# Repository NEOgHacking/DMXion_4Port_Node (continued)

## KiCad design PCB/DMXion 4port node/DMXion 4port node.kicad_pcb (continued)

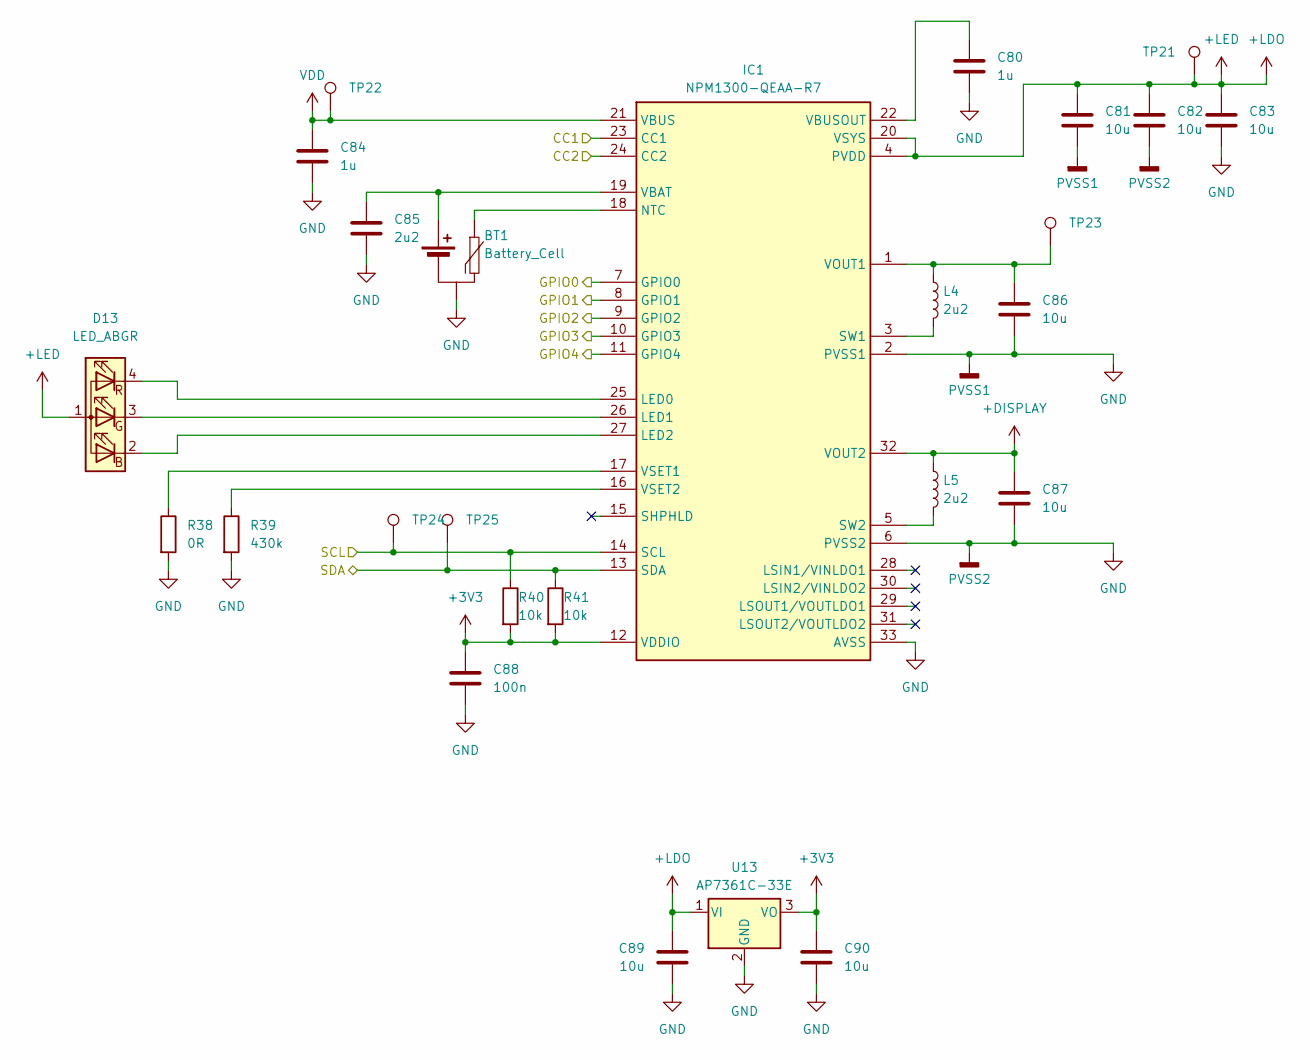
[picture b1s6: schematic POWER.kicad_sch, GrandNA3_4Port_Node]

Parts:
BT1: Battery_Cell; JST_XH_B3B-XH-A_1x03_P2.50mm_Vertical
C80, C84: 1u; C_0603_1608Metric
C81, C82, C83, C86, C87, C89, C90: 10u; C_0603_1608Metric
C85: 2u2; C_0603_1608Metric
C88: 100n; C_0603_1608Metric
D13: LED_ABGR; LED-SMD_4P-L1.6-W1.5-TR
IC1: NPM1300-QEAA-R7; QFN-32-1EP_5x5mm_P0.5mm_EP3.45x3.45mm_ThermalVias; Mouser Part Number 949-NPM1300-QEAA-R7
L4, L5: 2u2; L_0805_2012Metric
R38: 0R; R_0603_1608Metric
R39: 430k; R_0603_1608Metric
R40, R41: 10k; R_0603_1608Metric
TP21, TP22, TP23, TP24, TP25: TestPoint; TestPoint_Pad_D1.5mm
U13: AP7361C-33E; SOT-223-3_TabPin2

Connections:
+3V3: C88.1, C90.1, IC1.12 (VDDIO), R40.2, R41.2, U13.3 (VO); also elsewhere on the board
+DISPLAY: C87.1, IC1.32 (VOUT2), L5.1; also elsewhere on the board
+LDO: C81.1, C82.1, C83.1, C89.1, D13.1 (A), IC1.4 (PVDD), IC1.20 (VSYS), TP21.1 (1_1), U13.1 (VI); also elsewhere on the board
/Microcontroller/GPIO16: IC1.11 (GPIO4); also elsewhere on the board
/Microcontroller/GPIO17: IC1.10 (GPIO3); also elsewhere on the board
/Microcontroller/GPIO18: IC1.9 (GPIO2); also elsewhere on the board
/Microcontroller/GPIO19: IC1.8 (GPIO1); also elsewhere on the board
/Microcontroller/GPIO20: IC1.7 (GPIO0); also elsewhere on the board
/Microcontroller/GPIO22_I2C1_SDA: IC1.13 (SDA), R41.1, TP25.1 (1_1); also elsewhere on the board
/Microcontroller/GPIO23_I2C_SCL: IC1.14 (SCL), R40.1, TP24.1 (1_1); also elsewhere on the board
/POWER/CC1: IC1.23 (CC1); also elsewhere on the board
/POWER/CC2: IC1.24 (CC2); also elsewhere on the board
GND: BT1.2 (-), C80.2, C81.2, C82.2, C83.2, C84.2, C85.2, C86.2, C87.2, C88.2, C89.2, C90.2, IC1.2 (PVSS1), IC1.6 (PVSS2), IC1.33 (AVSS), R38.2, R39.2, U13.2 (GND); also elsewhere on the board
unnamed: BT1.1 (+), C85.1, IC1.19 (VBAT)
unnamed: BT1.3 (NTC), IC1.18 (NTC)
unnamed: D13.2 (BK), IC1.27 (LED2)
unnamed: D13.3 (GK), IC1.26 (LED1)
unnamed: D13.4 (RK), IC1.25 (LED0)
unnamed: IC1.3 (SW1), L4.2
unnamed: IC1.5 (SW2), L5.2
unnamed: C80.1, IC1.22 (VBUSOUT)
unnamed: C86.1, IC1.1 (VOUT1), L4.1, TP23.1 (1_1)
unnamed: IC1.17 (VSET1), R38.1
unnamed: IC1.16 (VSET2), R39.1
VDD: C84.1, IC1.21 (VBUS), TP22.1 (1_1); also elsewhere on the board

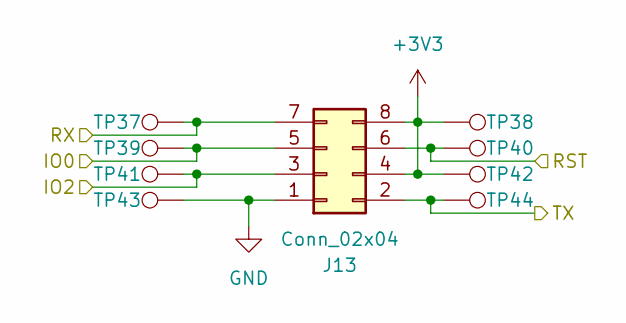
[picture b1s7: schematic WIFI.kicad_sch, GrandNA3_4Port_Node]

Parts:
J13: Conn_02x04; PinSocket_2x04_P2.54mm_Vertical
TP37, TP38, TP39, TP40, TP41, TP42, TP43, TP44: TestPoint; TestPoint_Pad_D1.5mm

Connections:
+3V3: J13.4, J13.8, TP38.1 (1_1), TP42.1 (1_1); also elsewhere on the board
/Microcontroller/GPIO11: J13.3, TP41.1 (1_1); also elsewhere on the board
/Microcontroller/GPIO12: J13.5, TP39.1 (1_1); also elsewhere on the board
/Microcontroller/GPIO13: J13.6, TP40.1 (1_1); also elsewhere on the board
/Microcontroller/GPIO14_UART1_TX: J13.7, TP37.1 (1_1); also elsewhere on the board
/Microcontroller/GPIO15_UART1_RX: J13.2, TP44.1 (1_1); also elsewhere on the board
GND: J13.1, TP43.1 (1_1); also elsewhere on the board

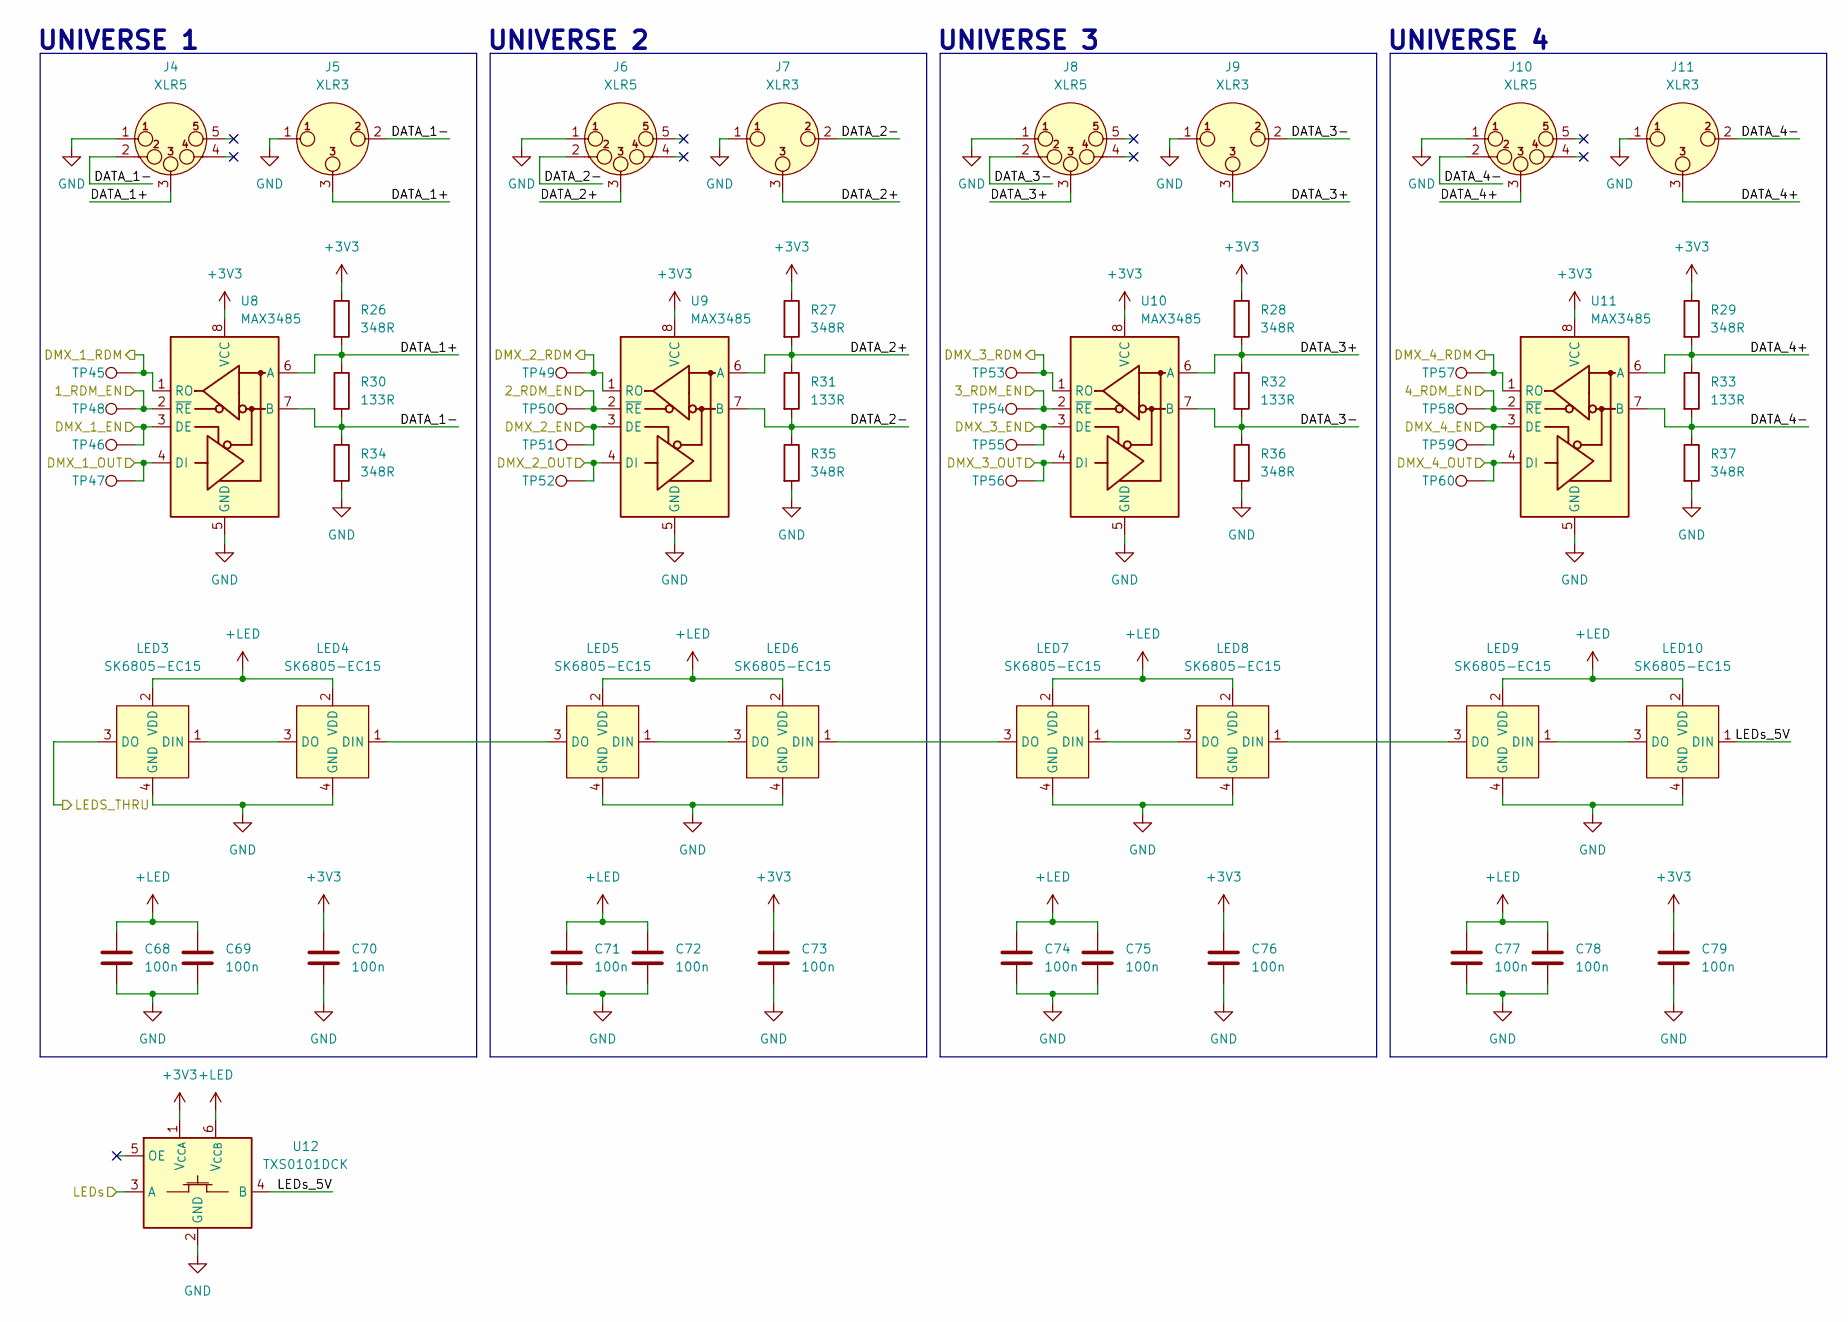
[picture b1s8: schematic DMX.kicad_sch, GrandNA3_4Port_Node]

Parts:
C68, C69, C70, C71, C72, C73, C74, C75, C76, C77, C78, C79: 100n; C_0603_1608Metric
J4, J6, J8, J10: XLR5; NC5FAH1-LR-DAE
J5, J7, J9, J11: XLR3; NC3FAH2-LR-DAE
LED3, LED4, LED5, LED6, LED7, LED8, LED9, LED10: SK6805-EC15; LED-SMD_4P-L1.5-W1.5-BL; LCSC Part C2890035
R26, R27, R28, R29, R34, R35, R36, R37: 348R; R_0603_1608Metric
R30, R31, R32, R33: 133R; R_0603_1608Metric
TP45, TP46, TP47, TP48, TP49, TP50, TP51, TP52, TP53, TP54, TP55, TP56, TP57, TP58, TP59, TP60: TestPoint; TestPoint_Pad_D1.5mm
U8, U9, U10, U11: MAX3485; SOIC-8_3.9x4.9mm_P1.27mm
U12: TXS0101DCK; SOT-363_SC-70-6

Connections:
+3V3: C70.1, C73.1, C76.1, C79.1, R26.1, R27.1, R28.1, R29.1, U8.8 (VCC), U9.8 (VCC), U10.8 (VCC), U11.8 (VCC), U12.1 (V_{CCA}); also elsewhere on the board
+LDO: C68.1, C69.1, C71.1, C72.1, C74.1, C75.1, C77.1, C78.1, LED3.2 (VDD), LED4.2 (VDD), LED5.2 (VDD), LED6.2 (VDD), LED7.2 (VDD), LED8.2 (VDD), LED9.2 (VDD), LED10.2 (VDD), U12.6 (V_{CCB}); also elsewhere on the board
/DMX/1_RDM_EN: TP48.1 (1_1), U8.2 (~RE); also elsewhere on the board
/DMX/2_RDM_EN: TP50.1 (1_1), U9.2 (~RE); also elsewhere on the board
/DMX/3_RDM_EN: TP54.1 (1_1), U10.2 (~RE); also elsewhere on the board
/DMX/4_RDM_EN: TP58.1 (1_1), U11.2 (~RE); also elsewhere on the board
/DMX/DATA_1+: J4.3, J5.3, R26.2, R30.1, U8.6 (A)
/DMX/DATA_1-: J4.2, J5.2, R30.2, R34.1, U8.7 (B)
/DMX/DATA_2+: J6.3, J7.3, R27.2, R31.1, U9.6 (A)
/DMX/DATA_2-: J6.2, J7.2, R31.2, R35.1, U9.7 (B)
/DMX/DATA_3+: J8.3, J9.3, R28.2, R32.1, U10.6 (A)
/DMX/DATA_3-: J8.2, J9.2, R32.2, R36.1, U10.7 (B)
/DMX/DATA_4+: J10.3, J11.3, R29.2, R33.1, U11.6 (A)
/DMX/DATA_4-: J10.2, J11.2, R33.2, R37.1, U11.7 (B)
/DMX/DMX_1_EN: TP46.1 (1_1), U8.3 (DE); also elsewhere on the board
/DMX/DMX_1_OUT: TP47.1 (1_1), U8.4 (DI); also elsewhere on the board
/DMX/DMX_1_RDM: TP45.1 (1_1), U8.1 (RO); also elsewhere on the board
/DMX/DMX_2_EN: TP51.1 (1_1), U9.3 (DE); also elsewhere on the board
/DMX/DMX_2_OUT: TP52.1 (1_1), U9.4 (DI); also elsewhere on the board
/DMX/DMX_2_RDM: TP49.1 (1_1), U9.1 (RO); also elsewhere on the board
/DMX/DMX_3_EN: TP55.1 (1_1), U10.3 (DE); also elsewhere on the board
/DMX/DMX_3_OUT: TP56.1 (1_1), U10.4 (DI); also elsewhere on the board
/DMX/DMX_3_RDM: TP53.1 (1_1), U10.1 (RO); also elsewhere on the board
/DMX/DMX_4_EN: TP59.1 (1_1), U11.3 (DE); also elsewhere on the board
/DMX/DMX_4_OUT: TP60.1 (1_1), U11.4 (DI); also elsewhere on the board
/DMX/DMX_4_RDM: TP57.1 (1_1), U11.1 (RO); also elsewhere on the board
/DMX/LEDs: U12.3 (A); also elsewhere on the board
/DMX/LEDs_5V: LED10.1 (DIN), U12.4 (B)
/LEDS_THRU: LED3.3 (DO); also elsewhere on the board
GND: C68.2, C69.2, C70.2, C71.2, C72.2, C73.2, C74.2, C75.2, C76.2, C77.2, C78.2, C79.2, J4.1, J5.1, J6.1, J7.1, J8.1, J9.1, J10.1, J11.1, LED3.4 (GND), LED4.4 (GND), LED5.4 (GND), LED6.4 (GND), LED7.4 (GND), LED8.4 (GND), LED9.4 (GND), LED10.4 (GND), R34.2, R35.2, R36.2, R37.2, U8.5 (GND), U9.5 (GND), U10.5 (GND), U11.5 (GND), U12.2 (GND); also elsewhere on the board
unnamed: LED3.1 (DIN), LED4.3 (DO)
unnamed: LED4.1 (DIN), LED5.3 (DO)
unnamed: LED5.1 (DIN), LED6.3 (DO)
unnamed: LED6.1 (DIN), LED7.3 (DO)
unnamed: LED7.1 (DIN), LED8.3 (DO)
unnamed: LED8.1 (DIN), LED9.3 (DO)
unnamed: LED9.1 (DIN), LED10.3 (DO)

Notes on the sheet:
UNIVERSE 1
UNIVERSE 3
UNIVERSE 4
UNIVERSE 2

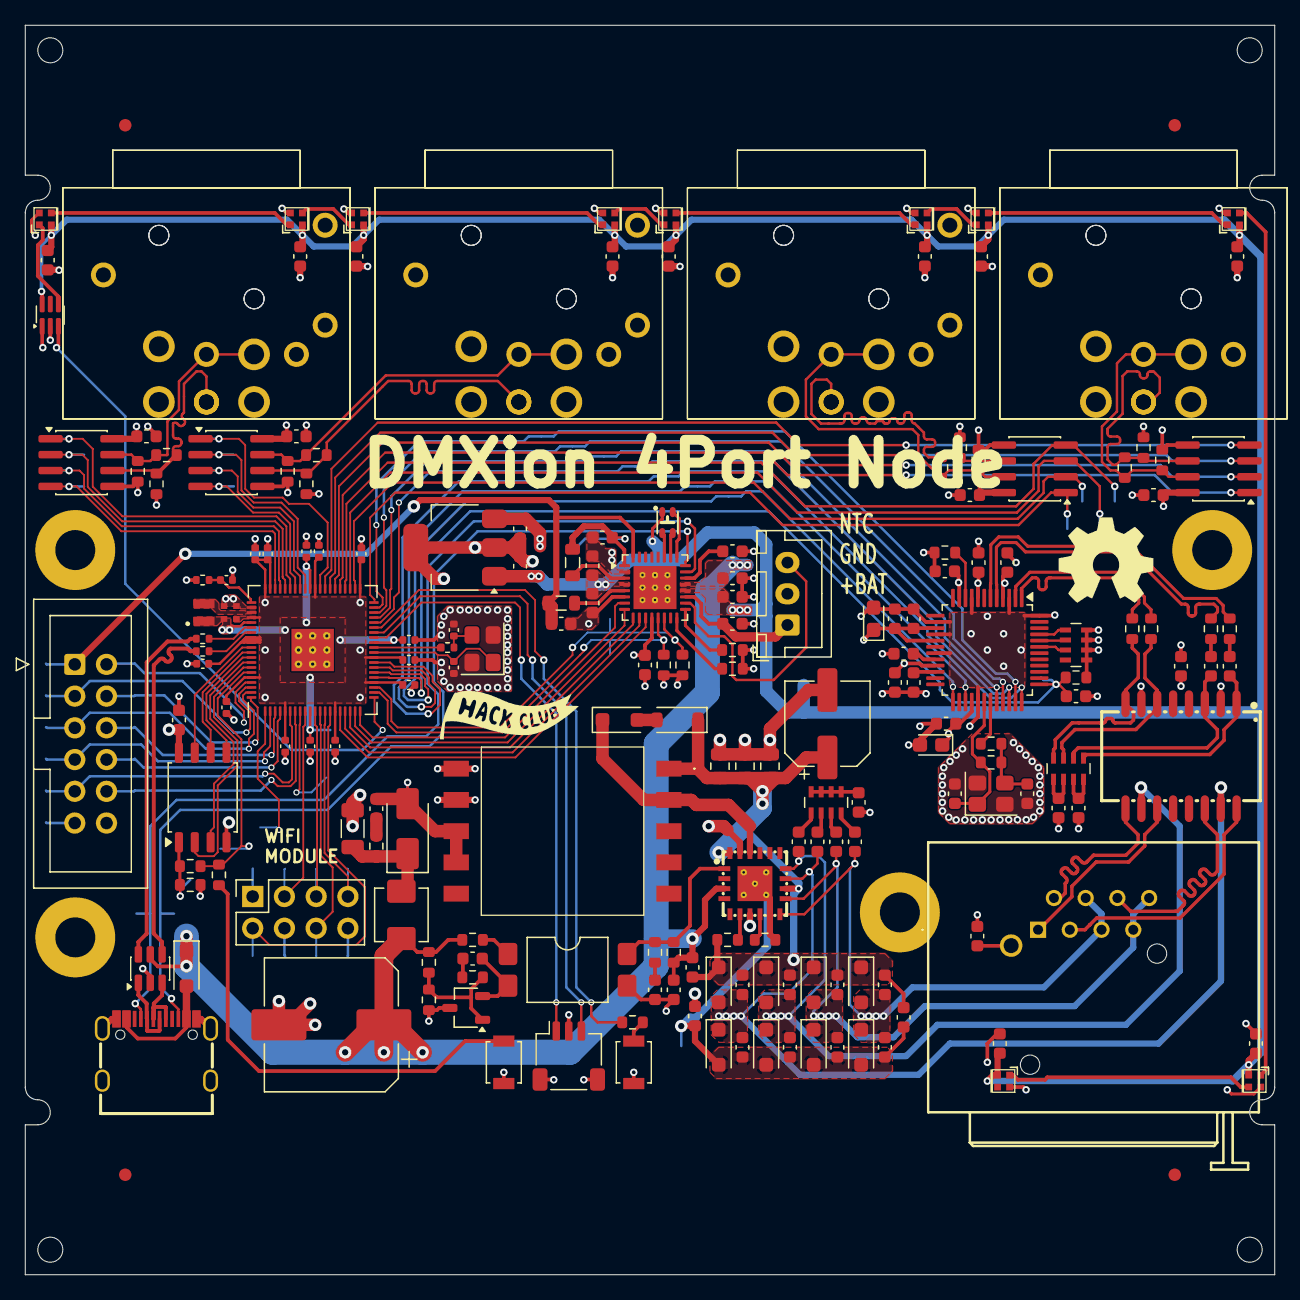
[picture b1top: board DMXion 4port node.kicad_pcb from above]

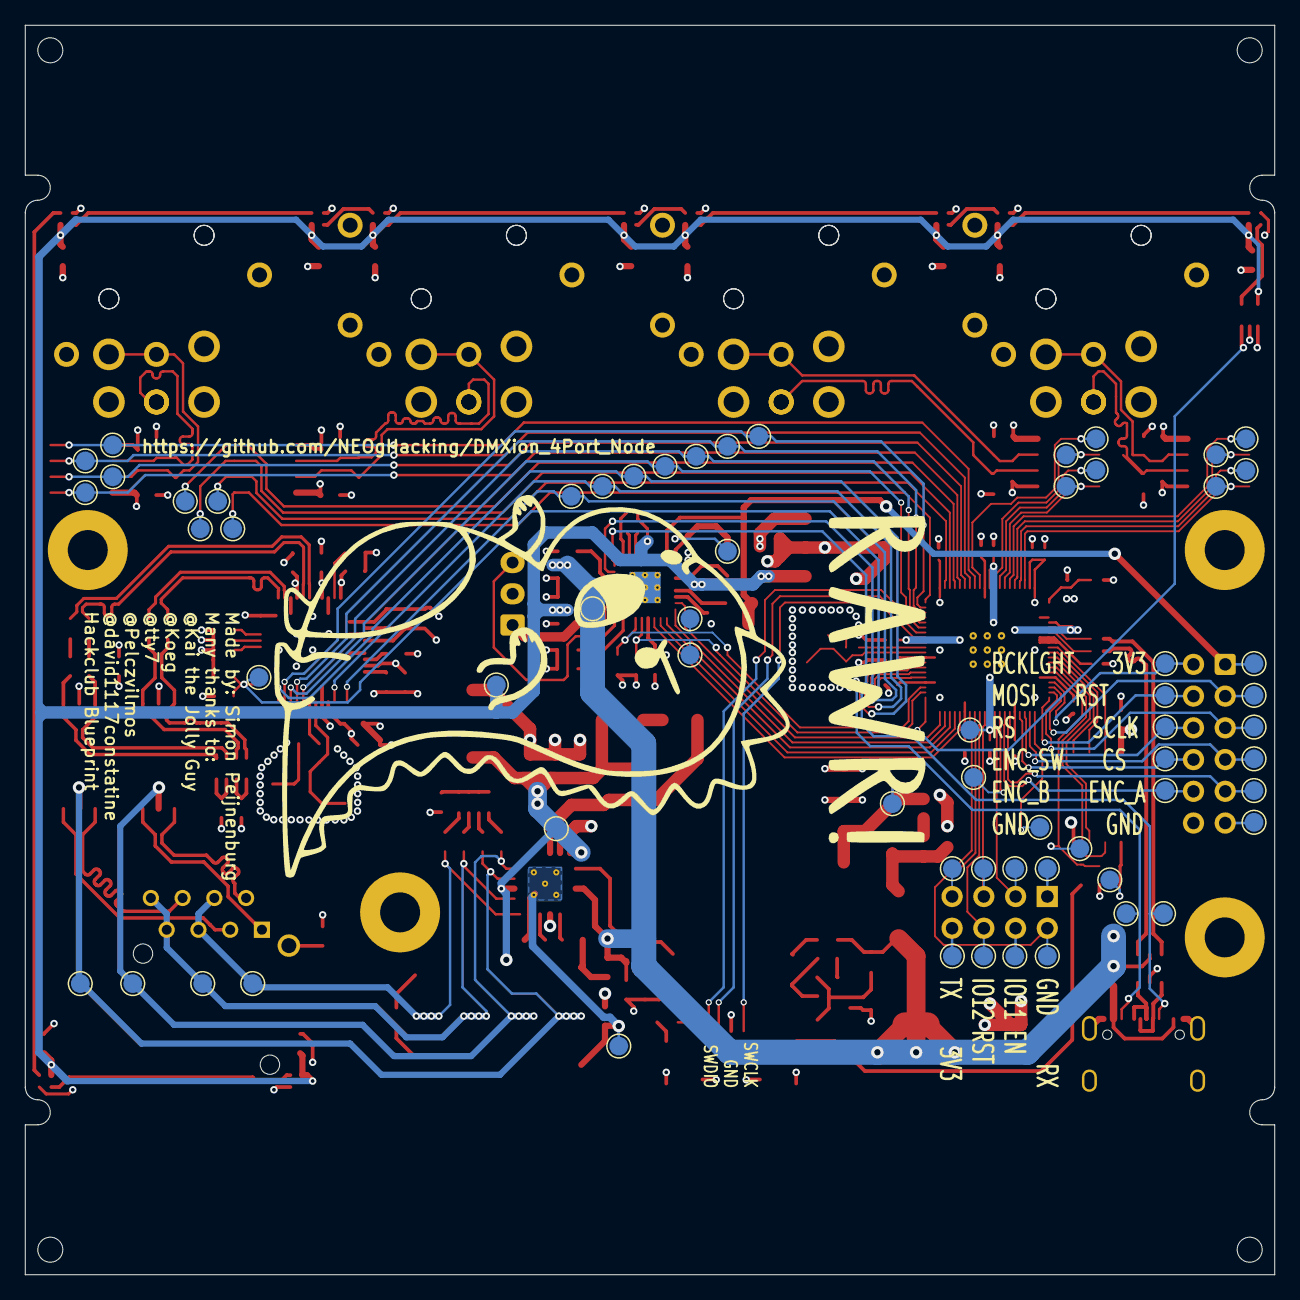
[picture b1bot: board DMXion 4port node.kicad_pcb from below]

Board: 4 copper layers, 100.0 x 100.0 mm, 269 parts (62 on the bottom side), 160 nets.

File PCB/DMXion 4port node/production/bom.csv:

Designator,Footprint,Quantity,Value,LCSC Part #
BT1,JST_XH_B3B-XH-A_1x03_P2.50mm_Vertical,1,Battery_Cell,
"C1, C10, C11, C12, C13, C3, C4, C5, C6, C7, C8, C9",0402,12,100n,
"C14, C15, C16, C2",0402,4,4u7,
"C17, C19",0402,2,15p,
"C18, C25, C26, C27, C28, C29, C30, C31, C38, C39, C41, C60, C61, C64, C66, C67, C68, C69, C70, C71, C72, C73, C74, C75, C76, C77, C78, C79, C88",0603,29,100n,
"C20, C21, C23, C33, C57",0603,5,10n,
"C22, C34, C35, C36, C37, C43, C44, C45, C46, C47, C63, C65",0603,12,1n,
"C24, C32",CP_EIA-2012-12_Kemet-R,2,10u,
"C40, C42",0603,2,6.8n,
"C48, C49",0603,2,10p,
"C50, C51, C52",0805,3,1u,
C53,CP_Elec_6.3x5.8,1,10u,
C54,0603,1,470p,
C55,CP_Elec_10x10.5,1,1000u,
C56,1206,1,100u,
C58,0603,1,4u7,
C59,0603,1,3.3n,
C62,0603,1,15n,
"C80, C84",0603,2,1u,
"C81, C82, C83, C86, C87, C89, C90",0603,7,10u,
C85,0603,1,2u2,
D1,D_SOD-123F,1,DSK24L,
D10,D_SMA,1,SS34,
D11,D_SOD-123,1,1N4148W,
D12,D_SOD-123F,1,DFTL30A,
D13,LED-SMD_4P-L1.6-W1.5-TR,1,LED_ABGR,
"D2, D3, D4, D5, D6, D7, D8, D9",D_SOD-123F,8,SL110PL-TP,
IC1,QFN-32-1EP_5x5mm_P0.5mm_EP3.45x3.45mm_ThermalVias,1,NPM1300-QEAA-R7,
J1,JST_SH_SM03B-SRSS-TB_1x03-1MP_P1.00mm_Horizontal,1,Conn_01x03_MountingPin,
"J10, J4, J6, J8",NC5FAH1-LR-DAE,4,XLR5,
"J11, J5, J7, J9",NC3FAH2-LR-DAE,4,XLR3,
J12,IDC-Header_2x06_P2.54mm_Vertical,1,IDC,
J13,PinSocket_2x04_P2.54mm_Vertical,1,Conn_02x04,
J2,USB-C_SMD-TYPE-C-31-M-12_1,1,USB_C_Receptacle_USB2.0_14P,
J3,NE8FAHLRDAE,1,RJ45,
L1,L_pol_2016,1,3.3u,
L2,L_Vishay_IHLP-1616,1,1u,
L3,XFMR-SMD_16P-L12.7-W7.1-P1.27-LS9.4-BL,1,H2019NLT,C110250
"L4, L5",0805,2,2u2,
"LED1, LED10, LED2, LED3, LED4, LED5, LED6, LED7, LED8, LED9",LED-SMD_4P-L1.5-W1.5-BL,10,SK6805-EC15,C2890035
"R1, R25, R3",0603,3,1k,
"R10, R11, R12, R13",0603,4,33R,
R14,0603,1,1M,
"R15, R20, R21, R38, R8",0603,5,0R,
R16,0603,1,10R,
R17,0603,1,12.4k,
R18,0603,1,4.99k,
R19,0603,1,2.05k,
R2,0402,1,33R,
R22,0603,1,36.5k,
R23,0603,1,12.1k,
R24,0603,1,24.9k,
"R26, R27, R28, R29, R34, R35, R36, R37",0603,8,348R,
"R30, R31, R32, R33",0603,4,133R,
R39,0603,1,430k,
"R4, R5",0402,2,27R,
"R40, R41, R7, R9",0603,4,10k,
R6,0402,1,1k,
"RN1, RN2",R_Array_Concave_4x0603,2,75R,
RN3,R_Array_Concave_4x0603,1,10k,
"SW1, SW2",SW_SPST_B3U-1000P,2,SW_Push,
T1,FA2924ALD,1,FA2805,
"TP1, TP10, TP11, TP12, TP13, TP14, TP15, TP16, TP17, TP18, TP19, TP2, TP20, TP21, TP22, TP23, TP24, TP25, TP26, TP27, TP28, TP29, TP3, TP30, TP31, TP32, TP33, TP34, TP35, TP36, TP37, TP38, TP39, TP4, TP40, TP41, TP42, TP43, TP44, TP45, TP46, TP47, TP48, TP49, TP5, TP50, TP51, TP52, TP53, TP54, TP55, TP56, TP57, TP58, TP59, TP6, TP60, TP61, TP62, TP7, TP8, TP9",TestPoint_Pad_D1.5mm,62,TestPoint,
U1,RP2350-QFN-80-1EP_10x10_P0.4mm_EP3.4x3.4mm_ThermalVias,1,RP2350B,
"U10, U11, U8, U9",SOIC-8_3.9x4.9mm_P1.27mm,4,MAX3485,
U12,SOT-363_SC-70-6,1,TXS0101DCK,
U13,SOT-223-3_TabPin2,1,AP7361C-33E,
U2,SOIC-8_5.3x5.3mm_P1.27mm,1,W25Q128JVS,
U3,SOT-23-6,1,USBLC6-2SC6,
U4,LQFP-48_7x7mm_P0.5mm,1,W5500,
U5,SMDIP-4_W9.53mm_Clearance8mm,1,VO618A-3X019T,
U6,QFN-20_L5.0-W5.0-P0.80-TL-EP2.8,1,SI3402-B-GMR,C510771
U7,TSOT-23,1,TLV431,
Y1,Crystal_SMD_3225-4Pin_3.2x2.5mm,1,ABM8-272-T3,
Y2,Crystal_SMD_3225-4Pin_3.2x2.5mm,1,ABM8-25.000MHZ-10-D1G-T,

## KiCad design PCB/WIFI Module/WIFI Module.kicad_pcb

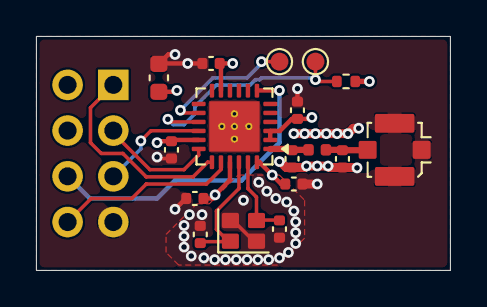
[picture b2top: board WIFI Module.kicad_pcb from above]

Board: 4 copper layers, 23.0 x 13.0 mm, 18 parts (1 on the bottom side), 13 nets.

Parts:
C1: 10u; C_0603_1608Metric
C2, C3, C4, C5, C6: 100n; C_0402_1005Metric
C7, C8: 3p; C_0402_1005Metric
C9, C10: 14p; C_0402_1005Metric
J1: Conn_01x01_Shielded; U.FL_Molex_MCRF_73412-0110_Vertical
J2: Conn_02x04; PinHeader_2x04_P2.54mm_Vertical
L1: 2n; L_0402_1005Metric
R1: 10k; R_0402_1005Metric
TP1, TP2: TestPoint; TestPoint_Pad_D1.0mm
U1: ESP8684; QFN-24-1EP_4x4mm_P0.5mm_EP2.8x2.8mm
Y1: Q22FA12800230; Crystal_SMD_SeikoEpson_FA128-4Pin_2.0x1.6mm

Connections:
+3V3: C1.1, C2.1, C3.1, C4.1, C5.1, C6.1, J2.2, R1.2, U1.2 (VDDA3P3), U1.3 (VDDA3P3), U1.11 (VDD3P3_RTC), U1.17 (VDD3P3_CPU), U1.21 (VDDA), U1.24 (VDDA)
/EN: J2.6, U1.7 (CHIP_EN)
/GPIO9: R1.1, TP2.1, U1.15 (GPIO9/BOOT)
/GPIO10: J2.5, U1.16 (GPIO10/FSPICS0)
/GPIO18: J2.3, U1.18 (GPIO18)
/RX: J2.1, U1.19 (U0RXD/GPIO19)
/TX: J2.8, U1.20 (U0TXD/GPIO20)
GND: C1.2, C2.2, C3.2, C4.2, C5.2, C6.2, C7.2, C8.2, C9.1, C10.1, J1.SH (Shield), J2.7, U1.25 (GND), Y1.2 (G), Y1.4 (G)
unnamed: C7.1, J1.1, L1.1
unnamed: C8.1, L1.2, U1.1 (ANT)
unnamed: TP1.1, U1.14 (GPIO8)
unnamed: C9.2, U1.22 (XTAL_N), Y1.1
unnamed: C10.2, U1.23 (XTAL_P), Y1.3

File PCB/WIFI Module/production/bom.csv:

Designator,Footprint,Quantity,Value,LCSC Part #
"C1_8, C1_7, C1_6, C1_5, C1_4, C1_3, C1_2, C1",0603,8,10u,
"C10_8, C10_7, C10_6, C10_5, C10_4, C10_3, C10_2, C10, C9_8, C9_7, C9_6, C9_5, C9_4, C9_3, C9_2, C9",0402,16,14p,
"C2_8, C2_7, C2_6, C2_5, C2_4, C2_3, C2_2, C2, C3_8, C3_7, C3_6, C3_5, C3_4, C3_3, C3_2, C3, C4_8, C4_7, C4_6, C4_5, C4_4, C4_3, C4_2, C4, C5_8, C5_7, C5_6, C5_5, C5_4, C5_3, C5_2, C5, C6_8, C6_7, C6_6, C6_5, C6_4, C6_3, C6_2, C6",0402,40,100n,
"C7_8, C7_7, C7_6, C7_5, C7_4, C7_3, C7_2, C7, C8_8, C8_7, C8_6, C8_5, C8_4, C8_3, C8_2, C8",0402,16,3p,
"J1_8, J1_7, J1_6, J1_5, J1_4, J1_3, J1_2, J1",U.FL_Molex_MCRF_73412-0110_Vertical,8,Conn_01x01_Shielded,
"J2_8, J2_7, J2_6, J2_5, J2_4, J2_3, J2_2, J2",PinHeader_2x04_P2.54mm_Vertical,8,Conn_02x04,
"L1_8, L1_7, L1_6, L1_5, L1_4, L1_3, L1_2, L1",0402,8,2n,
"R1_8, R1_7, R1_6, R1_5, R1_4, R1_3, R1_2, R1",0402,8,10k,
"TP1_8, TP1_7, TP1_6, TP1_5, TP1_4, TP1_3, TP1_2, TP1, TP2_8, TP2_7, TP2_6, TP2_5, TP2_4, TP2_3, TP2_2, TP2",TestPoint_Pad_D1.0mm,16,TestPoint,
"U1_8, U1_7, U1_6, U1_5, U1_4, U1_3, U1_2, U1",QFN-24-1EP_4x4mm_P0.5mm_EP2.8x2.8mm,8,ESP8684,
"Y1_8, Y1_7, Y1_6, Y1_5, Y1_4, Y1_3, Y1_2, Y1",Crystal_SMD_SeikoEpson_FA128-4Pin_2.0x1.6mm,8,Q22FA12800230,

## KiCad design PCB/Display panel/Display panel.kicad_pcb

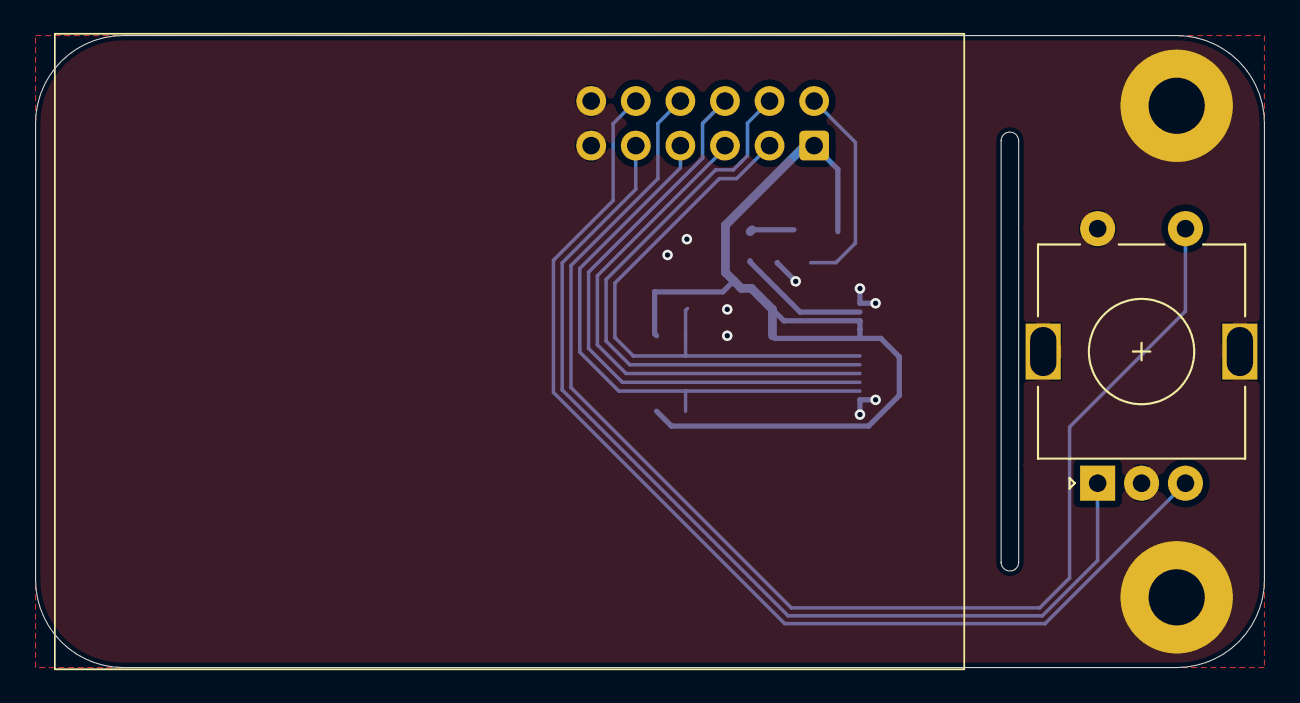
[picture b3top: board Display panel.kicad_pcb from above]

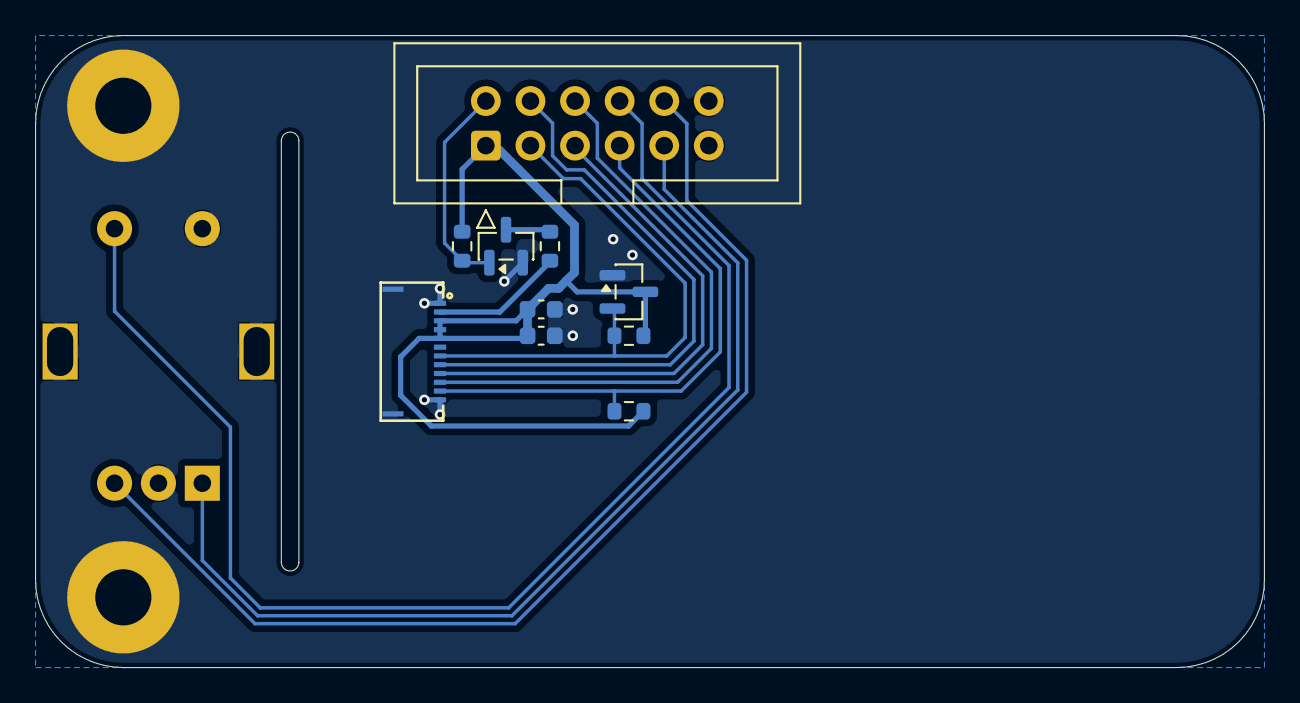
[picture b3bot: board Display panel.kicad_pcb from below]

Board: 2 copper layers, 70.0 x 36.0 mm, 13 parts (10 on the bottom side), 13 nets.

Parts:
C1: 4u7; C_0603_1608Metric
C2: 100n; C_0603_1608Metric
H1, H2: MountingHole_Pad; MountingHole_3.2mm_M3_Pad
J1: Conn_01x12_MountingPin; FPC-SMD_5034801200
J2: IDC; IDC-Header_2x06_P2.54mm_Vertical
Q2: BSS138; SOT-23
R1: 10R; R_0603_1608Metric
R2, R3, R4: 10k; R_0603_1608Metric
SW2: EC11E18244AU; RotaryEncoder_Alps_EC11E-Switch_Vertical_H20mm
U1: APX803S-31SA-7; SOT-23

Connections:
+3V3: C1.1, C2.1, J1.3, J1.4, J1.5, J2.1, R2.2, R3.1, R4.2, U1.3 (VCC)
/BACKLIGHT: J2.2, Q2.1 (G), R2.1
/CS: J1.11, J2.7, R3.2
/ENC_A: J2.9, SW2.A
/ENC_B: J2.10, SW2.B
/ENC_SW: J2.8, SW2.S1
/LED_K: J1.2, R1.2
/MOSI: J1.8, J2.4
/RESET: J1.7, J2.3, R4.1, U1.2 (~RESET)
/RS: J1.10, J2.6
/SCLK: J1.9, J2.5
GND: C1.2, C2.2, H1.1, H2.1, J1.1, J1.12, J1.MP (MountPin), J2.11, J2.12, Q2.2 (S), SW2.C, SW2.MP, SW2.S2, U1.1 (GND)
unnamed: Q2.3 (D), R1.1

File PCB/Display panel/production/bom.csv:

Designator,Footprint,Quantity,Value,LCSC Part #
"C1_2, C1",0603,2,4u7,
"C2_2, C2",0603,2,100n,
"J1_2, J1",FPC-SMD_5034801200,2,Conn_01x12_MountingPin,
"J2_2, J2",IDC-Header_2x06_P2.54mm_Vertical,2,IDC,
"Q2_2, Q2",SOT-23,2,BSS138,
"R1_2, R1",0603,2,10R,
"R2_2, R2, R3_2, R3, R4_2, R4",0603,6,10k,
"SW2_2, SW2",RotaryEncoder_Alps_EC11E-Switch_Vertical_H20mm,2,EC11E18244AU,
"U1_2, U1",SOT-23,2,APX803S-31SA-7,C129757

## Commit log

2026-03-02 Create README.md for Assets directory
    Add a README for the Assets directory
2026-03-02 added more assets
2026-03-02 Update README with schematics and PCB details
    Added schematics and PCB images to the README.
2026-03-02 Revise README.md for improved clarity
    Updated description for clarity and corrected minor grammatical issues.
2026-03-03 Updated BOM
2026-03-03 Made BOM collapsible
2026-03-03 Added firware for the wifi module
2026-03-03 Add usage section to README
    Added usage instructions for the product, detailing firmware upload and setup process.
2026-03-03 Add README for 3D design project
2026-03-03 Add link to Onshape document in README
2026-03-03 Added step file
2026-03-14 Updated the PCB Allot
2026-03-15 EVEN MORE PCB updates
2026-03-16 Fixed allot of problems
    Added a new LDO for the 3.3V rail to support the load i miscalculated 💀
2026-03-16 Fixed RP2350 power layout
2026-03-17 Testpoints and GND1 Fill
2026-03-23 Renamed device
2026-03-23 Renamed assest
2026-03-24 Auto stash before merge of "main" and "origin/main"
2026-04-01 Added more testpoints
2026-04-01 Even more testpads
2026-04-03 Fixed allot of PCB mistakes and added more silkscreen
